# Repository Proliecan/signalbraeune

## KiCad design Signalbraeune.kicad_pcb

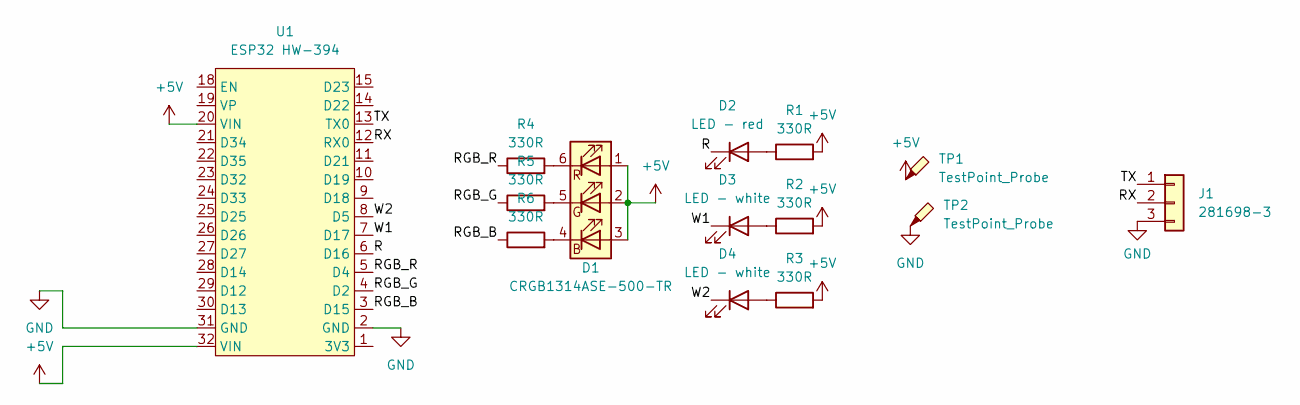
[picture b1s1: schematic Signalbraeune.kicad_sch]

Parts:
D1: CRGB1314ASE-500-TR
D2: LED - red; LED_1206_3216Metric_Pad1.42x1.75mm_HandSolder
D3, D4: LED - white; LED_1206_3216Metric_Pad1.42x1.75mm_HandSolder
J1: 281698-3; PinHeader_1x03_P2.54mm_Horizontal
R1, R2, R3, R4, R5, R6: 330R; R_1206_3216Metric_Pad1.30x1.75mm_HandSolder
TP1, TP2: TestPoint_Probe; TestPoint_Pad_D1.0mm
U1: ESP32 HW-394; DIP-32_W15.24mm

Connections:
+5V: D1.1 (AR), D1.2 (GA), D1.3 (AB), R1.2, R2.2, R3.2, TP1.1, U1.20 (VIN), U1.32 (VIN)
/R: D2.1 (K), U1.6 (D16)
/RGB_B: R6.1, U1.3 (D15)
/RGB_G: R5.1, U1.4 (D2)
/RGB_R: R4.1, U1.5 (D4)
/RX: J1.2, U1.12 (RX0)
/TX: J1.1, U1.13 (TX0)
/W1: D3.1 (K), U1.7 (D17)
/W2: D4.1 (K), U1.8 (D5)
GND: J1.3, TP2.1, U1.2 (GND), U1.31 (GND)
unnamed: D1.4 (BK), R6.2
unnamed: D1.5 (GK), R5.2
unnamed: D1.6 (RK), R4.2
unnamed: D2.2 (A), R1.1
unnamed: D3.2 (A), R2.1
unnamed: D4.2 (A), R3.1

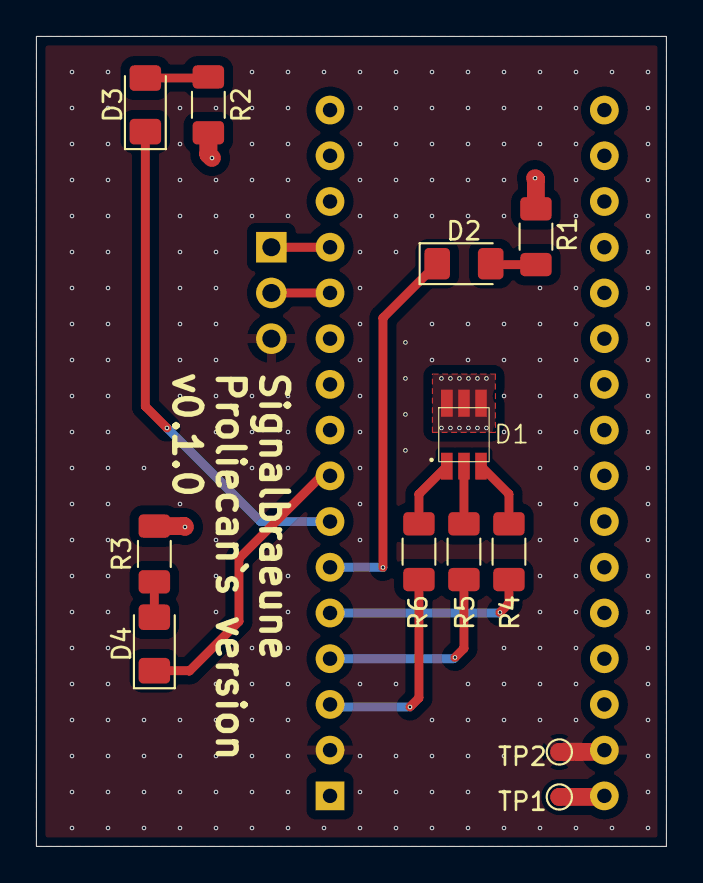
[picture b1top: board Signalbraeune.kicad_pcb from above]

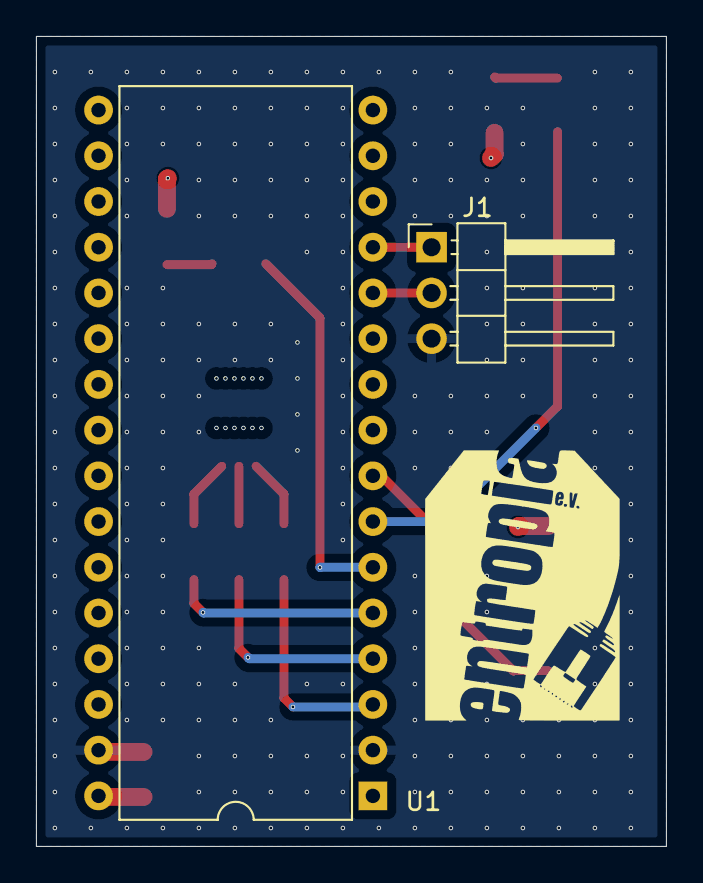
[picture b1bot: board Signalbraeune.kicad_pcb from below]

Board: 4 copper layers, 35.0 x 45.0 mm, 15 parts (3 on the bottom side), 16 nets.

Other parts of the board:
 : teebeutel_15mm

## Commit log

2024-09-10 v0.1.0
